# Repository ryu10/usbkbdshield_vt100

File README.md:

# USB Keyboard Shield for VT100

__Rev. 2.1__

## About

This shield connects a standard USB keyboard to the DEC VT100 terminal.

### Features

* All keys on the VT100 keyboard are mapped to the USB keyboard keys.
* VT100 keyboard LEDs and bell are emulated on the shield PCB.

The Gerber file, BOM, schematics and Arduino sketch for the shield are included in this repo. For the steps to assemble, program and connect the shields, please see the sections below.

__Note:__ this shield uses the USB Host Shield from Circuits@Home.

Please use the information in this repo at your own risk. No warranty or guarantee is provided.

## Required Components

- USB Keyboard Shield for VT100 (the shield from this repo)
- [USB Host Shield by Circuits@Home](https://www.circuitsathome.com/arduino_usb_host_shield_projects/), the "full-sized board"
- Arduino Uno
- Keyboard cable for VT100 (see "Keyboard Cable" below)
- USB Keyboard

## Steps

1. Assemble the shield
2. Build a keyboard cable
3. Program the Arduino
4. Connect the shields and cables

The details of each step are described in the next few sections.

## Assemble the Shield

The USB Keyboard Shield for VT100 can be assembled using the following info:

- PCB Gerber File: [usbkbd_vt100_2_1_gerber.zip](./usbkbd_vt100_2_1_gerber.zip)
- Schematic: [usbkbd_vt100_sch.pdf](./usbkbd_vt100_sch.pdf)
- BOM: [usbkbd_vt100_BOM_2_1.pdf](./usbkbd_vt100_BOM_2_1.pdf)

## Build the Keyboard Cable

To make the keyboard cable, connect these components:

 - 1/4 inch stereo plug/cable
 - 5-pin header connector

__PIN CONNECTIONS__

| Pin | Plug |  Value |
|-|-|-|
| 1* | - | (spk+)* |
| 2* | - | (spk-)* |
| 3 | Tip | +12V |
| 4 | Sleeve | GND |
| 5 | Ring | Signal |

  \* optional

The pin connector is attached to J1 header on the USB Keyboard shield for VT100. The stereo plug is connected to the keyboard port on VT100 terminal.

## Program the Arduino Uno

It is recommended to program the Arduino Uno before attaching the shields.

1. Install [USB Host Shield Library 2.0](https://github.com/felis/USB_Host_Shield_2.0) and [Timer1 Library](http://playground.arduino.cc/Code/Timer1) into Arduino IDE.

2. Clone or download this project.

3. Open the sketch `usbkeyboardvt100/usbkeyboardvt100.ino` in Arduino IDE, and program the Arduino Uno.

### Configuration Options

There are two options in `usbkeyboardvt100.ino`:
```
// SWAPCAPS: If defined, LeftCtrl and CapsLock are swapped on USB Keyboard.
#define SWAPCAPS

// SWAPLFBAR: If defined, swap LineFeed and '|\' key codes for VT100.
//#define SWAPLFBAR
```

Comment out/uncomment the `#define` lines as needed.

## Connect the Shields and Cables

1. Connect the USB keyboard to the USB connector on the USB Host Shield.
2. Connect the keyboard cable for VT100 to the J1 header on the USB Keyboard Shield.
3. Connect the keyboard cable to the keyboard port on VT100 terminal.
4. Stack and connect the Arduino Uno, the USB Host Shield, and the USB Keyboard Shield, in this order, from the bottom to the top (see the iamge below).
5. No external power supply is needed. The power is supplied via the VT100 keyboard cable.

## Key Mappings

Some hard-to-guess keys:

| VT100 Key | USB Keyboard Key |
|-|-|
| SET UP | F1, SysRq |
| CTRL | Caps Lock |
| CAPS LOCK | Left Ctrl |
| BREAK | Break |
| LINE FEED | End |
| NO SCROLL | Scroll Lock |
| PF1 | Num Lock, F9 |
| PF2 | (numpad) /, F10 |
| PF3 | (numpad) *, F11 |
| PF4 | Page Up, F12 |
|(numpad) , | (numpad) + |

The key mappings are defined in `usb_key_tbl[]` in `usbkeyboardvt100.h`. Also see "Configuration Options" above.

## Reference Configuration

The following configuration was used during development of this shield:

- USB Host Shield 2.0
- Arduino Uno R3
- VT100-WA / VT-180
- USB Keyboards: HP K1500 / Logitech K310

## Known Issues

1. Keyboard connected via a USB hub is not supported.

## GPL

The code is released under the GNU General Public License.

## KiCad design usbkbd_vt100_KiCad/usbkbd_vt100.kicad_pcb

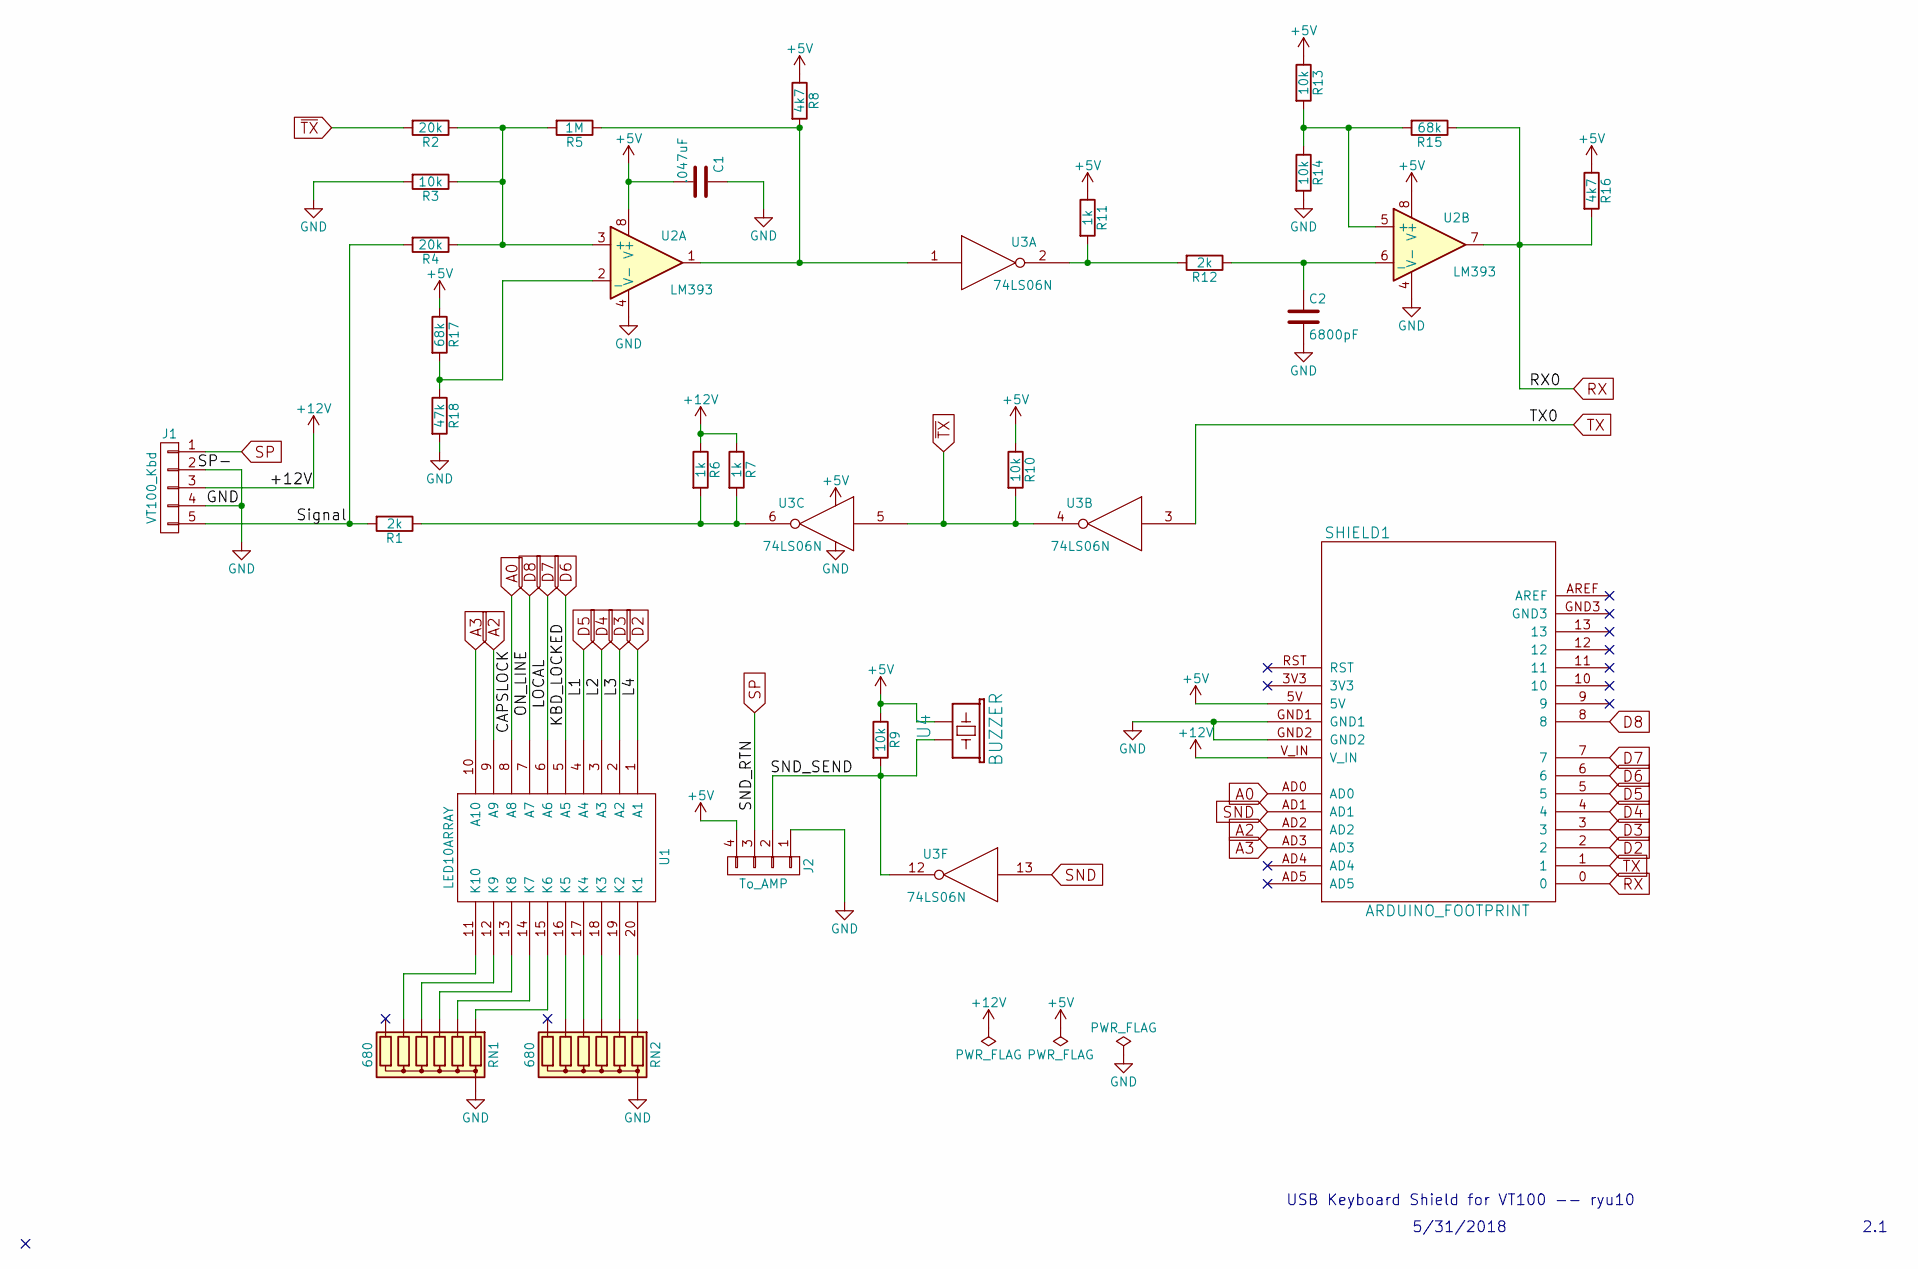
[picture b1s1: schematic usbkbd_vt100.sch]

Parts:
C1: .047uF; C_Disc_D5.0mm_W2.5mm_P2.50mm
C2: 6800pF; C_Disc_D5.0mm_W2.5mm_P2.50mm
J1: VT100_Kbd; Pin_Header_Angled_1x05
J2: To_AMP; Pin_Header_Straight_1x04
R1, R12: 2k; R_Axial_DIN0204_L3.6mm_D1.6mm_P7.62mm_Horizontal
R2, R4: 20k; R_Axial_DIN0204_L3.6mm_D1.6mm_P7.62mm_Horizontal
R3, R9, R10, R13, R14: 10k; R_Axial_DIN0204_L3.6mm_D1.6mm_P7.62mm_Horizontal
R5: 1M; R_Axial_DIN0204_L3.6mm_D1.6mm_P7.62mm_Horizontal
R6, R7, R11: 1k; R_Axial_DIN0204_L3.6mm_D1.6mm_P7.62mm_Horizontal
R8, R16: 4k7; R_Axial_DIN0204_L3.6mm_D1.6mm_P7.62mm_Horizontal
R15, R17: 68k; R_Axial_DIN0204_L3.6mm_D1.6mm_P7.62mm_Horizontal
R18: 47k; R_Axial_DIN0204_L3.6mm_D1.6mm_P7.62mm_Horizontal
RN1, RN2: 680; R_Array_SIP7
SHIELD1: ARDUINO_FOOTPRINT; ARDUINO_SHIELD_NOICSP
U1: LED10ARRAY; DIP-20_W7.62mm
U2: LM393; DIP-8_W7.62mm_Socket
U3: 74LS06N; DIP-14_W7.62mm_Socket
U4: BUZZER; Buzzer_12x9.5RM7.6

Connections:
+5V: C1.2, J2.4, R8.1, R9.1, R10.1, R11.1, R13.1, R16.1, R17.1, SHIELD1.5V, U2.8 (V+), U3.14 (VCC), U4.1 (POS)
+12V: J1.3, R6.1, R7.1, SHIELD1.V_IN
/SND_SEND: J2.2, R9.2, U3.12, U4.2 (GND)
/Signal: J1.5, R1.2, R4.2
A0: SHIELD1.AD0, U1.8 (A8)
A2: SHIELD1.AD2, U1.9 (A9)
A3: SHIELD1.AD3, U1.10 (A10)
D2: SHIELD1.2, U1.1 (A1)
D3: SHIELD1.3, U1.2 (A2)
D4: SHIELD1.4, U1.3 (A3)
D5: SHIELD1.5, U1.4 (A4)
D6: SHIELD1.6, U1.5 (A5)
D7: SHIELD1.7, U1.6 (A6)
D8: SHIELD1.8, U1.7 (A7)
GND: C1.1, C2.2, J1.2, J1.4, J2.1, R3.2, R14.2, R18.2, RN1.1 (common), RN2.1 (common), SHIELD1.GND1, SHIELD1.GND2, U2.4 (V-), U3.7 (GND)
unnamed: C2.1, R12.1, U2.6 (_)
unnamed: R1.1, R6.2, R7.2, U3.6
unnamed: R2.1, R3.1, R4.1, R5.2, U2.3 (+)
unnamed: R5.1, R8.2, U2.1, U3.1
unnamed: R11.2, R12.2, U3.2
unnamed: R13.2, R14.1, R15.2, U2.5 (+)
unnamed: R17.2, R18.1, U2.2 (_)
unnamed: RN1.2 (R1), U1.15 (K6)
unnamed: RN1.3 (R2), U1.14 (K7)
unnamed: RN1.4 (R3), U1.13 (K8)
unnamed: RN1.5 (R4), U1.12 (K9)
unnamed: RN1.6 (R5), U1.11 (K10)
unnamed: RN2.2 (R1), U1.20 (K1)
unnamed: RN2.3 (R2), U1.19 (K2)
unnamed: RN2.4 (R3), U1.18 (K3)
unnamed: RN2.5 (R4), U1.17 (K4)
unnamed: RN2.6 (R5), U1.16 (K5)
RX: R15.1, R16.2, SHIELD1.0, U2.7
SND: SHIELD1.AD1, U3.13
SP: J1.1, J2.3
TX: SHIELD1.1, U3.3
~TX: R2.2, R10.2, U3.4, U3.5

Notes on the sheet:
USB Keyboard Shield for VT100 -- ryu10
2.1
5/31/2018

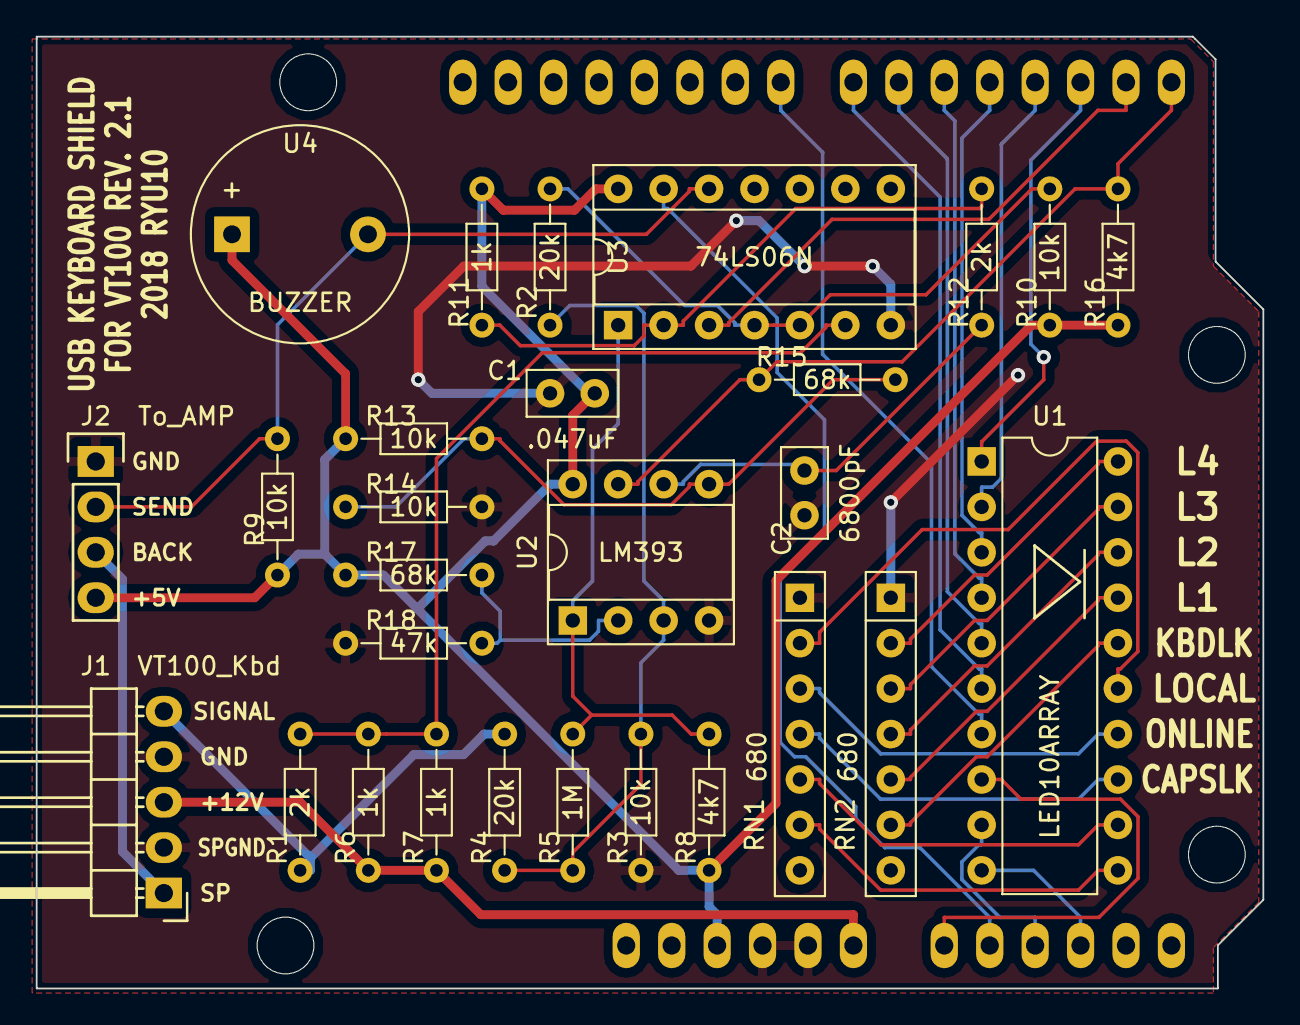
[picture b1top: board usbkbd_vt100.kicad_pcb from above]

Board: 2 copper layers, 68.6 x 53.2 mm, 29 parts (0 on the bottom side), 37 nets.

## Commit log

2018-06-15 Rev2.1 release for GitHub
2018-06-19 doc: fixed a typo in readme
2018-09-19 Updated the rev2.1 BOM
2018-09-19 Update the BOM
2019-02-21 readme: install step for Timer1
2019-04-01 Update Readme.md
    mintor adjustments
